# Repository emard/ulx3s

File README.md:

# ULX3S PCB

[ULX3S](http://radiona.org/ulx3s) = [University digital Logic](https://www.fer.unizg.hr/en/course/diglog) Learning
Xtensible board release 3 with SDRAM,
Successor of [ULX2S](http://github.com/emard/ulx2s).

[Manual](/doc/MANUAL.md) *
[Quickstart Binaries](http://github.com/emard/ulx3s-bin) *
[ULX3S at Kitspace](https://kitspace.org/boards/github.com/emard/ulx3s)

3D preview

Prototypes available
at [SKRIPTARNICA](http://skriptarnica.hr/vijest.aspx?newsID=1466),
local shop inside of [FER](https://www.fer.unizg.hr/) university.

This is a small (94x51 mm) standalone FPGA board 
for education, research and general purpose, with a full 
featured selection of chips which I all wanted on
a low-cost PCB, but haven't found on the market.
It's open source and open hardware because if it is
good for our development of [f32c](http://github.com/f32c/f32c) SOC,
it should be also good to other projects.

ULX3S will carry all digital logic on our
research, [education](https://www.fer.unizg.hr/en/course/diglog) and
[makerspace](https://radiona.org) projects in next 5 years.

ULX3S is standalone embeddable gadget with onboard display, buttons,
storage, WiFi and compatible connectors.

ULX3S can do things no other board can.

ULX3S can self-reflash with a bitstream sent
remotely from web interface over WiFi or from SD
card browsed by onboard OLED display and buttons.

ULX3S can completely power down and wakeup from
battery backed RTC.

ULX3S has rich range of chips and connectivity
required for many other open source projects:
SDRAM, USB, PS/2, SDCARD, Digital Video, FLASH, RTC, I2C, OLED, AUDIO, ADC,
onboard FM/ASK antenna 88-433.92 MHz and 56 GPIO pins routed as differential
pairs and have pinout that is PMOD compatible. There are 12 true
differential bidirectional pairs and 16 single-ended pairs.

ULX3S is sufficiently equipped to
emulate [Amiga](https://github.com/emard/Minimig_ECS) retro
computer and run its games, but can do much more like
running [Linux](https://twitter.com/fpga_dave/status/1053290842809683968).

[Schematics](/doc/schematics.pdf) and PCB started with KiCAD 4.
After version v1.8 project switched to KiCAD 5 PCB editor:

    kicad ulx3s.pro

View generated gerbers

    gerbv -p plot/ulx3s.gvp

# Features

FPGA: Lattice ECP5 [LFE5U-85F-6BG381C](http://www.latticesemi.com/view_document?document_id=50461) (12/25/45/85K LUT)

USB: FTDI [FT231XS](https://www.ftdichip.com/Support/Documents/DataSheets/ICs/DS_FT231X.pdf) (500kbit JTAG and 3Mbit USB-serial)

GPIO: 56 pins (12 true differential pairs, 16 single-ended pairs),
[PMOD](https://reference.digilentinc.com/_media/pmod:pmod:originalPmodInterfaceSpecification.pdf) compatible
with power out 3.3V/1A 2.5V/1.5A

RAM: 16-bit SDRAM [MT48LC32M16](https://www.micron.com/-/media/client/global/Documents/Products/Data%20Sheet/DRAM/256Mb_sdr.pdf) (8/16/32/64 MB)

Flash: Quad-SPI Flash [IS25LP128F](http://www.issi.com/WW/pdf/25LP-WP128F.pdf) (4/8/16 MB for FPGA config and user data)

Storage: Micro-SD slot

LEDs: 11 (8 blink-LEDs, 2 USB LEDs, 1 WiFi LED)

Buttons: 7 (4 direction, 2 fire, 1 power button)

Audio: 3.5 mm jack with 4 contacts (analog stereo + digital audio or composite video)

Video: GPDI connector with 3.3V-5V I2C bidirectional level shifter

Display: placeholder for 0.96" SPI COLOR OLED [SSD1331](https://drive.google.com/file/d/0B5lkVYnewKTGRlpxcEdWaXNvWnM/view)

WiFi+bluetooth: placeholder for [ESP-32](https://www.espressif.com/sites/default/files/documentation/esp32_datasheet_en.pdf) (Standalone JTAG web interface over WiFi)

Antenna: 88-108/433 MHz FM/ASK onboard

ADC: 8 channels, 12 bit, 1 MSa/s [MAX11125](https://datasheets.maximintegrated.com/en/ds/MAX11120-MAX11128.pdf) (4/8-ch, 8/10/12-bit, 0.5/1 MSa/s)

Power: 3 Switching voltage regulators: 1.1V, 2.5V, 3.3V (1.5/2A)

Clock: 25 MHz onboard, external differential clock input

Low power sleep: 5uA/5V standby, RTC [MCP7940N](http://ww1.microchip.com/downloads/en/DeviceDoc/20005010F.pdf) clock wakeup, power button, 32768 Hz quartz and battery

GPDI is General Purpose Differential Interface,
Electrically LVDS, mostly TMDS tolerant
female receptacle more-or-less compatible
with digital monitors/TVs

# Production

Independent production
like [q3k](https://twitter.com/q3k/status/1029010026269167618) or
[samlittlewood](https://twitter.com/samlittlewood/status/1108531208001077250) is
welcome and desirable under conditions of [modified MIT LICENSE](/LICENSE.md).
If you do manual assembly here is [minimal parts list](/doc/MINIMAL.md).

ZIP the gerbers and send them to manufacturer:

    zip -r /tmp/ulx3s.zip plot/ulx3s

If you are going to order this project by yourself, it is important
what manufacturer to choose for PCBA (PCB and Assembly) service.

Parts can be ordered from [Detailed BOM](/doc/ulx3s_bom.csv)
or from [ULX3S at Kitspace](https://kitspace.org/boards/github.com/emard/ulx3s),
which automatically submits [Simplified 1-click BOM](/1-click-bom.tsv) by
clicking on "Digikey" or "Mouser" button. On each click, Digikey and Mouser will keep
accumulating the BOM in the shopping cart. Number of unique parts on Digikey and Mouser
should be equal but DigiKey may split some parts (LEDs) in multiple rows.
To reset shopping cart, click "New Cart" or "New Basket".
Kitspace may be updated with about 1 day delay after this project update.

Choose PCBA manufacturer which can produce PCB of IPC CLASS 3 quality,
5/5 mil trace resolution and 0.2 mm holes.
Avoid manufacturer who claims "quality" and "satisfaction" but doesn't
really know what will be IPC CLASS rating for this project.

PCBA manufacturer prices for the parts should be approximately equal as those
from distributors like [Mouser](http://www.mouser.com) or [DigiKey](http://www.digikey.com).
Avoid any PCBA manufacturer who asks 3$ for the 1$ part or 40$ for the 30$ part.
Select [Mouser](http://www.mouser.com) language/location icon to PCBA manufacturer
country of origin and $-currency to check is PCBA manufacturer telling the truth
about prices.

Before soldering the parts, ask manufacturer for [pictures](/pic/ulx3sb-v18.jpg) of PCB.
CLASS 3 demands, among other things, that all drill holes stay inside of VIA pads.
If some holes [break-out](/pic/ulx3sb-v18-breakout-c19.png) from pads,
ask manufacturer to make new PCBs with better drill and copper layer alignment.

[PCBCART](http://www.pcbcart.com) offers CLASS 3 quality and assembly at reasonable cost.
Prices for the parts are equal to [Mouser](http://www.mouser.com).

Don't pay everything at once. Following payment phases during the
PCBA production are recommended:

    1. Pay for the parts
    2. Manufacturer orders the parts and optionally negotiates with you about part numbers.
       Depending on market availability, some parts may come in different physical package.
    3. Send updated gerbers which fit to ordered parts.
    4. Pay for PCB
    5. Manufacturer sends pictures of produced PCB for your inspection.
       If anything looks suspicious, ask also for X-ray imaging.
    6. Pay for the assembly and shipping.

Nobody wants quality issues, so it is good to ask if manufacturer has qualified personnel
able to follow instructions 
for [ULX3S self-test](https://github.com/emard/ulx3s-bin) before shipping.
## This readme clearly shows how to use make the project step by step in simple ways happy making :)

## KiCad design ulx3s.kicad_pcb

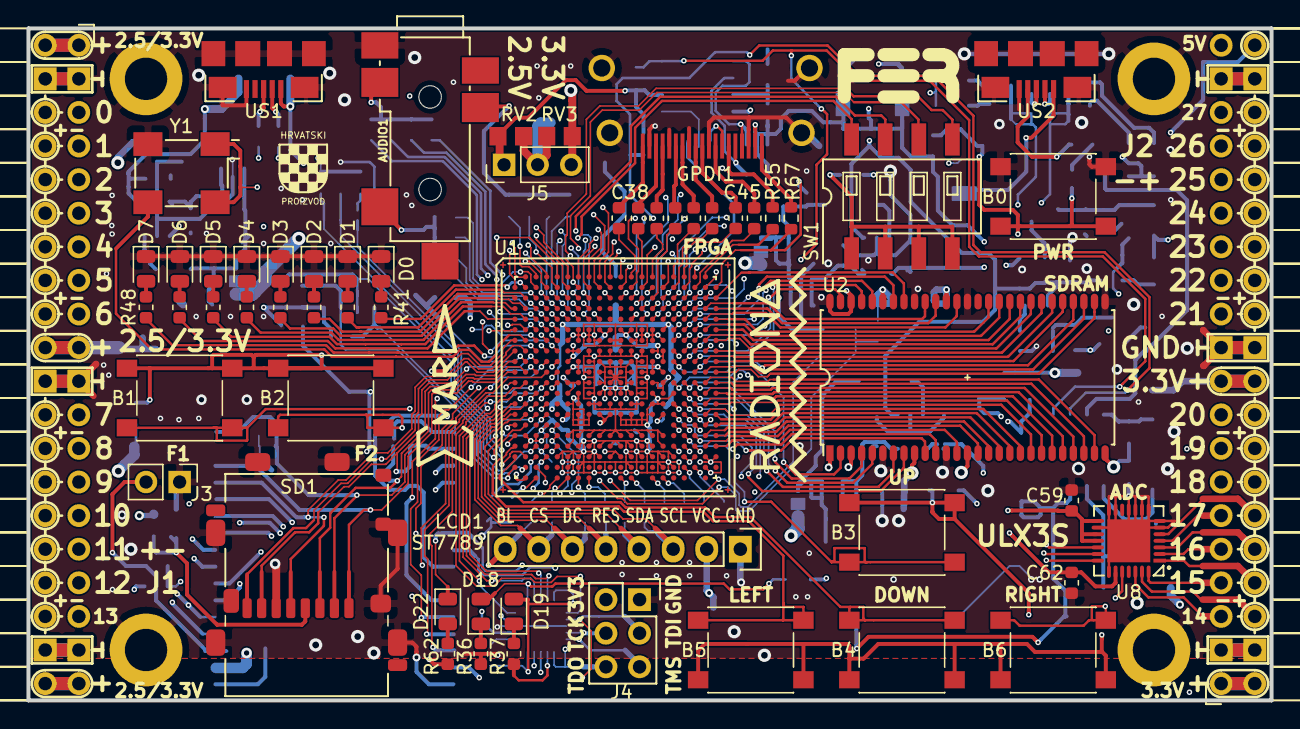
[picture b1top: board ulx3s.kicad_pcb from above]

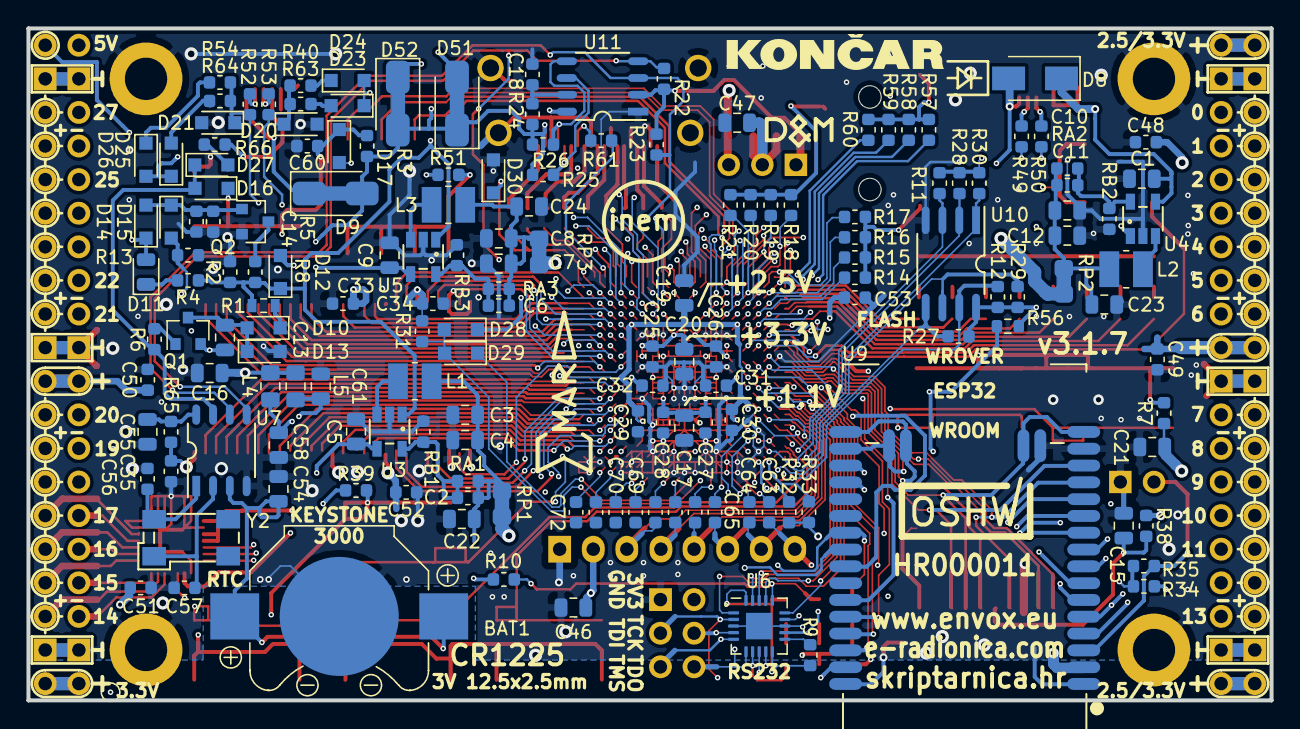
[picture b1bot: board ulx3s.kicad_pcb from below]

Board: 4 copper layers, 94.0 x 50.8 mm, 234 parts (167 on the bottom side), 287 nets.

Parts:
AE1: 433MHz; TestPoint_Pad_D1.0mm
AUDIO1: JACK_TRS_6PINS; CUI_SJ-43516-SMT
B0, B1, B2, B3, B4, B5, B6: PTS645; SW_SPST_PTS645
BAT1: CR1225; Keystone_3000_1x12mm-CoinCell
C1, C3, C4, C5, C7, C8, C9, C11, C12, C15, C21, C54, C55, C58, C61: 22uF; C_0805_2012Metric
C2, C6, C10, C18: 100pF; C_0603_1608Metric
C13, C16, C17, C19, C20, C22, C23, C24, C46, C47: 2.2uF; C_0805_2012Metric
C14, C59, C60, C62: 220nF; C_0603_1608Metric
C25, C26, C27, C28, C29, C30, C31, C32, C33, C34, C35, C38, C39, C40, C41, C42, C43, C44, C45, C48, C49, C50, C51, C52, C53, C63, C64, C65, C66, C67, C68, C69, C70, C71, C72: 22nF; C_0603_1608Metric
C56, C57: 4.7pF; C_0603_1608Metric
D0, D4, D11, D19: RED; LED_0805_2012Metric
D1, D5: ORANGE; LED_0805_2012Metric
D2, D6, D18: GREEN; LED_0805_2012Metric
D3, D7, D22: BLUE; LED_0805_2012Metric
D8: STPS2L40AF; D_SMA
D9, D51, D52: 0; D_SMA_Jumper_NC
D10, D13, D14, D16, D17, D23, D24, D25, D26, D27, D28, D29: 1N914; D_SOD-323_HandSoldering
D12, D15: BAT54W; D_SOD-323_HandSoldering
D20, D21, D30: 3.6V; D_SOD-323_HandSoldering
D&M: dm2mm
EMARD: emard12mm
EMARD#2: emard12mm
GPDI1: GPDI-D; CONN-10029449-111RLF
H1, H2, H3, H4: HOLE; MountingHole_3.2mm_M3_ISO14580_Pad
HR: HR; hrvatski
J1, J2: CONN_02X20; Socket_Strip_Angled_2x20
J3: WIFI_OFF; PinHeader_1x02_P2.54mm_Vertical
J4: CONN_02X03; Socket_Strip_Straight_2x03
J5: VJ1; PinHeader_1x03_P2.54mm_Vertical
L1, L2, L3: 2.2uH; L_1008_1210
L4, L5: 33uH; L_0805_2012Metric_Pad1.15x1.40mm_HandSolder
LCD1: ST7789; st7789
OSHW: OSHW2mm; oshw
Q1: BC857; SOT-23
Q2: 2N7002; SOT-23
R1, R3, R4, R25, R26, R30: 4.7k; R_0603_1608Metric
R2: 18k; R_0603_1608Metric
R5: 2.2M; R_0603_1608Metric
R6, R8, R14, R18, R29, R40, R54, R57, R66: 1.1k; R_0603_1608Metric
R7, R10, R17, R21, R39, R51, R60: 130; R_0603_1608Metric
R9, R13, R31, R32, R33, R34, R56, R63, R64: 15k; R_0603_1608Metric
R11, R12, R27, R28, R55: 10k; R_0603_1608Metric
R15, R19, R35, R36, R37, R41, R42, R43, R44, R45, R46, R47, R48, R58, R61, R62, R65, R67: 549; R_0603_1608Metric
R16, R20, R59: 270; R_0603_1608Metric
R22, R23: 3.3k; R_0603_1608Metric
R24: 100k; R_0603_1608Metric
R38: 0.47; R_0603_1608Metric
R49, R50, R52, R53: 27; R_0603_1608Metric
RA1, RA2, RA3: 15k; R_0603_1608Metric
RB1: 18k; R_0603_1608Metric
RB2: 4.7k; R_0603_1608Metric
RB3: 3.3k; R_0603_1608Metric
RP1, RP2, RP3: 0; R_0805_2012Metric_Pad1.29x1.40mm_HandSolder_Jumper_NC
RV2, RV3: 0; R_0805_2012Metric_Pad1.29x1.40mm_HandSolder
SD1: 104031-0811; SCHD3A100-104031-0811
SW1: SW_DIP_x04; SW_DIP_x4_W8.61mm_Slide_LowProfile
U1: LFE5U-85F-6BG381C; BGA-381_pitch0.8mm_dia0.4mm
U2: MT48LC16M16A2TG; TSOP54
U3, U4, U5: TLV62569DBV; TSOT-25
U6: FT231XQ; FT231X-QFN-20-1EP_4x4mm_P0.5mm_EP2x2mm
U7: MCP7940NT; SOT96-1
U8: MAX11125; MAX1112x-TQFN-28-1EP_5x5mm_Pitch0.5mm
U9: ESP32
U10: IS25LP128F-JBLE; SOA008-150-208mil
U11: PCA9306D; SM8
US1, US2: MICRO_USB; USB-MICRO-B-FCI-10118192-0001LF
Y1: FNETHE025; Crystal_SMD_7050_4Pads
Y2: 32768Hz; Crystal_SMD_ABS25
fer: fer; fer4mm6
koncar: koncar
radiona: radiona

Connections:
2V5_3V3: C26.1, C47.1, C48.1, C49.1, C53.1, J1.1, J1.2, J1.19, J1.20, J1.39, J1.40, J5.2, R51.1, RV2.2, RV3.1, U1.F9, U1.F10, U1.H6, U1.H7, U1.J6
+1V1: C17.1, C27.1, C28.1, RP1.2, U1.H8, U1.H9, U1.H10, U1.H11, U1.H12, U1.H13, U1.J8, U1.J13, U1.K8, U1.K13, U1.L8, U1.L13, U1.M8, U1.M13, U1.N8, U1.N9, U1.N10, U1.N11, U1.N12, U1.N13, U1.T6, U1.T7, U1.T8, U1.T9, U1.T10, U1.T11, U1.T12, U1.T13, U1.T14, U1.T15, U1.U6, U1.U15
+2V5: C19.1, C29.1, C30.1, J5.1, R22.1, R23.1, RP2.2, RV2.1, U1.F6, U1.F15, U1.P6, U1.P15, U1.V10, U1.V11, U1.V17, U1.V18, U11.2
+3V3: C16.1, C20.1, C21.1, C25.1, C31.1, C32.1, C33.1, C34.1, C35.1, C46.1, C50.1, C51.1, C52.1, D11.2, D14.1, J2.1, J2.2, J2.19, J2.20, J4.2, J5.3, L4.1, L5.1, LCD1.2, R7.1, R11.1, R12.1, R27.1, R28.1, R29.1, R30.1, R31.1, R32.1, R33.1, R34.1, R38.2, R39.1, R56.1, R62.2, R65.1, RP3.2, RV3.2, U1.F11, U1.F12, U1.H14, U1.H15, U1.J15, U1.L6, U1.L7, U1.L14, U1.L15, U1.M6, U1.M15, U1.P9, U1.P10, U1.T2, U1.T3, U1.T4, U1.U2, U2.1, U2.3, U2.9, U2.14, U2.27, U2.43, U2.49, U9.2, U10.8, U11.8, Y1.1, Y1.4
+5V: C1.1, C5.1, C9.1, C13.1, D8.1, D9.2, D51.1, D52.2, GPDI1.18, Q1.2, R3.1, R24.1, R25.1, R26.1, U3.4, U4.4, U5.4
/analog/ADC3V3: C58.1, C59.1, L4.2, U8.15, U8.17, U8.18
/analog/ADCD3V3: C61.1, C62.1, L5.2, U8.23
/analog/AUDIO_L: AUDIO1.2, R14.2, R15.2, R16.2, R17.2
/analog/AUDIO_R: AUDIO1.3, R18.2, R19.2, R20.2, R21.2
/analog/AUDIO_V: AUDIO1.4, R57.2, R58.2, R59.2, R60.2
/blinkey/ALED0: D0.2, R41.2
/blinkey/ALED1: D1.2, R42.2
/blinkey/ALED2: D2.2, R43.2
/blinkey/ALED3: D3.2, R44.2
/blinkey/ALED4: D4.2, R45.2
/blinkey/ALED5: D5.2, R46.2
/blinkey/ALED6: D6.2, R47.2
/blinkey/ALED7: D7.2, R48.2
/blinkey/BTNPUL: B1.1, B2.1, R7.2
/blinkey/BTNPUR: B3.1, B4.1, B5.1, B6.1, R39.2
/blinkey/LED_PWREN: D18.1, R36.1
/blinkey/LED_TXLED: D19.1, R37.2
/blinkey/LED_WIFI: D22.2, R62.1
/blinkey/SWPU: R51.2, SW1.1, SW1.2, SW1.3, SW1.4
/flash/FLASH_MISO: R28.2, U1.V2, U10.2
/flash/FLASH_MOSI: R27.2, U1.W2, U10.5
/flash/FLASH_SCK: R29.2, U1.U3, U10.6
/flash/FLASH_nCS: R30.2, U1.R2, U10.1
/flash/FLASH_nHOLD: R12.2, U1.W1, U10.7
/flash/FLASH_nWP: R11.2, U1.Y2, U10.3
/flash/FPGA_DONE: R32.2, U1.Y3
/flash/FPGA_INITN: R33.2, U1.V3
/flash/FPGA_PROGRAMN: D28.2, D29.2, R31.2, U1.W3
/gpdi/GPDI_CEC: GPDI1.13, R61.1
/gpdi/GPDI_CLK+: C44.2, GPDI1.10
/gpdi/GPDI_CLK-: C45.2, GPDI1.12
/gpdi/GPDI_D0+: C42.2, GPDI1.7
/gpdi/GPDI_D0-: C43.2, GPDI1.9
/gpdi/GPDI_D1+: C40.2, GPDI1.4
/gpdi/GPDI_D1-: C41.2, GPDI1.6
/gpdi/GPDI_D2+: C38.2, GPDI1.1
/gpdi/GPDI_D2-: C39.2, GPDI1.3
/gpdi/GPDI_HPD: GPDI1.19, R67.2
/gpdi/GPDI_UTIL: GPDI1.14, R55.2
/gpdi/VREF2: C18.1, R24.2, U11.7
/gpio/IN5V: D51.2, J2.39
/gpio/OUT5V: D52.1, J2.40
/power/FB1: C2.2, RA1.2, RB1.2, U3.5
/power/FB2: C10.2, RA2.2, RB2.2, U4.5
/power/FB3: C6.2, RA3.2, RB3.2, U5.5
/power/FTDI_nSUSPEND: D12.2, R10.1
/power/HOLD: D11.1, R4.1
/power/L1: L1.1, U3.3
/power/L2: L2.1, U4.3
/power/L3: L3.1, U5.3
/power/OSCI_32k: C56.2, U7.1, Y2.4
/power/OSCO_32k: C57.2, U7.2, Y2.1
/power/P1V1: C2.1, C3.1, C4.1, C22.1, L1.2, RA1.1, RP1.1
/power/P2V5: C10.1, C11.1, C12.1, C23.1, L2.2, RA2.1, RP2.1
/power/P3V3: C6.1, C7.1, C8.1, C24.1, L3.2, RA3.1, RP3.1
/power/PWREN: D12.1, R1.2, R2.1, R4.2, R8.1, U3.1, U4.1, U5.1
/power/RTCVDD: C55.1, R65.2, U7.8
/power/SHD: Q2.3, R8.2
/power/SHUT: C14.1, D14.2, D15.1, Q2.1, R5.1
/power/VBAT: BAT1.1, C54.1, U7.3
/power/WAKE: D10.1, R1.1
/power/WAKEUPn: D16.2, D27.1, R6.2, U7.7
/power/WKUP: C13.2, D10.2, D13.1, Q1.3
/power/WKn: Q1.1, R6.1
/serdes/SRCLKN: C68.1, U1.Y12
/serdes/SRCLKP: C67.2, U1.Y11
/serdes/SRXN00: C64.1, U1.Y6
/serdes/SRXN01: C66.1, U1.Y8
/serdes/SRXN10: C70.1, U1.Y15
/serdes/SRXP00: C63.2, U1.Y5
/serdes/SRXP01: C65.2, U1.Y7
/serdes/SRXP10: C69.2, U1.Y14
/serdes/STXN11: C72.1, U1.W18
/serdes/STXP11: C71.2, U1.W17
/usb/ANT_433MHz: AE1.1, U1.G1
/usb/FPD+: R53.2, US2.3
/usb/FPD-: R52.2, US2.2
/usb/FTD+: R50.2, US1.3
/usb/FTD-: R49.2, US1.2
/usb/US2VBUS: D9.1, US2.1
/wifi/SD3V3: C15.1, R38.1, SD1.4
/wifi/WIFIEN: J3.2, R35.2, U9.3
ADC_CSn: U1.R17, U8.20
ADC_MISO: U1.U16, U8.24
ADC_MOSI: U1.R16, U8.21
ADC_SCLK: U1.P17, U8.19
AUDIO_L0: R14.1, U1.E4
AUDIO_L1: R15.1, U1.D3
AUDIO_L2: R16.1, U1.C3
AUDIO_L3: R17.1, U1.B3
AUDIO_R0: R18.1, U1.A3
AUDIO_R1: R19.1, U1.B5
AUDIO_R2: R20.1, U1.D5
AUDIO_R3: R21.1, U1.C5
AUDIO_V0: R57.1, U1.H5
AUDIO_V1: R58.1, U1.F2
AUDIO_V2: R59.1, U1.F5
AUDIO_V3: R60.1, U1.E5
BTN_D: B4.2, U1.V1
BTN_F1: B1.2, U1.R1
BTN_F2: B2.2, U1.T1
BTN_L: B5.2, U1.U1
BTN_PWRn: D17.2, U1.D6
BTN_R: B6.2, U1.H16
BTN_U: B3.2, U1.R18
CLK_25MHz: U1.G2, Y1.3
FPDI_CEC: R61.2, U1.A18
FPDI_CLK+: C44.1, U1.A17
FPDI_CLK-: C45.1, U1.B18
FPDI_D0+: C42.1, U1.A16
FPDI_D0-: C43.1, U1.B16
FPDI_D1+: C40.1, U1.A14
FPDI_D1-: C41.1, U1.C14
FPDI_D2+: C38.1, U1.A12
FPDI_D2-: C39.1, U1.A13
FPDI_HPD: D30.1, R67.1, U1.B20
FPDI_SCL: R23.2, U1.E12, U7.6, U11.3
FPDI_SDA: R22.2, U1.B19, U7.5, U11.4
FPDI_UTIL: R55.1, U1.A19
FT2V5: D19.2, R9.2, U6.10, U6.20
FTDI_RXD: U1.L4, U6.1
FTDI_TXD: U1.M1, U6.17
FTDI_TXDEN: U1.L3, U6.15
FTDI_nDTR: U1.N1, U6.18
FTDI_nRTS: U1.M3, U6.19
FTDI_nRXLED: U1.L5, U6.14
FTDI_nSLEEP: D18.2, R10.2, U6.16
FTDI_nTXLED: R37.1, U6.7
GN0: J1.5, U1.C11
GN1: J1.7, U1.A11
GN2: J1.9, U1.B10
GN3: J1.11, U1.C10
GN4: J1.13, U1.A8
GN5: J1.15, U1.B8
GN6: J1.17, U1.C7
GN7: J1.23, U1.B6
GN8: J1.25, U1.A5
GN9: J1.27, U1.B1
GN10: J1.29, U1.B4
GN11: J1.31, U1.E3
GN12: J1.33, U1.F3, U9.8
GN13: J1.35, U1.G5, U9.5
GN14: J2.5, U1.U17, U8.26
GN15: J2.7, U1.P16, U8.28
GN16: J2.9, U1.M17, U8.2
GN17: J2.11, U1.L17, U8.4
GN18: J2.13, U1.H17
GN19: J2.15, U1.G18
GN20: J2.17, U1.E17
GN21: J2.23, U1.D17
GN22: J2.25, U1.C15
GN23: J2.27, U1.C17
GN24: J2.29, U1.D16
GN25: J2.31, U1.E14
GN26: J2.33, U1.C13
GN27: J2.35, U1.E13
GND: AUDIO1.1, B0.2, BAT1.2, C1.2, C3.2, C4.2, C5.2, C7.2, C8.2, C9.2, C11.2, C12.2, C14.2, C15.2, C16.2, C17.2, C18.2, C19.2, C20.2, C21.2, C22.2, C23.2, C24.2, C25.2, C26.2, C27.2, C28.2, C29.2, C30.2, C31.2, C32.2, C33.2, C34.2, C35.2, C46.2, C47.2, C48.2, C49.2, C50.2, C51.2, C52.2, C53.2, C54.2, C55.2, C56.1, C57.1, C58.2, C59.2, C60.2, C61.2, C62.2, D0.1, D1.1, D2.1, D3.1, D4.1, D5.1, D6.1, D7.1, D13.2, D20.2, D21.2, D30.2, GPDI1.0, GPDI1.2, GPDI1.5, GPDI1.8, GPDI1.11, GPDI1.17, H1.1, H2.1, H3.1, H4.1, J1.3, J1.4, J1.21, J1.22, J1.37, J1.38, J2.3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
GP0: J1.6, U1.B11
GP1: J1.8, U1.A10
GP2: J1.10, U1.A9
GP3: J1.12, U1.B9
GP4: J1.14, U1.A7
GP5: J1.16, U1.C8
GP6: J1.18, U1.C6
GP7: J1.24, U1.A6
GP8: J1.26, U1.A4
GP9: J1.28, U1.A2
GP10: J1.30, U1.C4
GP11: J1.32, U1.F4
GP12: J1.34, U1.G3, U9.9
GP13: J1.36, U1.H4, U9.4
GP14: J2.6, U1.U18, U8.27
GP15: J2.8, U1.N17, U8.1
GP16: J2.10, U1.N16, U8.3
GP17: J2.12, U1.L16, U8.5
GP18: J2.14, U1.H18
GP19: J2.16, U1.F17
GP20: J2.18, U1.D18
GP21: J2.24, U1.C18
GP22: J2.26, U1.B15
GP23: J2.28, U1.B17
GP24: J2.30, U1.C16
GP25: J2.32, U1.D14
GP26: J2.34, U1.B13
GP27: J2.36, U1.D13
GPDI_SCL: GPDI1.15, R25.2, U11.6
GPDI_SDA: GPDI1.16, R26.2, U11.5
JTAG_TCK: J4.4, U1.T5, U6.4, U9.30
JTAG_TDI: J4.3, U1.R5, U6.2, U9.37
JTAG_TDO: J4.6, U1.V4, U6.6, U9.6
JTAG_TMS: D22.1, J4.5, U1.U5, U6.5, U9.29
LED0: R41.1, U1.B2
LED1: R42.1, U1.C2
LED2: R43.1, U1.C1
LED3: R44.1, U1.D2
LED4: R45.1, U1.D1
LED5: R46.1, U1.E2
LED6: R47.1, U1.E1
LED7: R48.1, U1.H3
unnamed: D23.2, R63.1
unnamed: D24.1, R40.1
unnamed: D25.2, R64.1
unnamed: D26.1, R54.2
unnamed: D27.2, R66.2
OLED_BL: C63.1, LCD1.8, U1.J4
OLED_CLK: C68.2, LCD1.3, U1.P4
OLED_CS: C64.2, LCD1.7, U1.N2
OLED_DC: C65.1, LCD1.6, U1.P1
OLED_MOSI: C67.1, LCD1.4, U1.P3
OLED_RES: C66.2, LCD1.5, U1.P2
PWRBTn: B0.1, C60.1, D16.1, D17.1, D28.1, R3.2
SDRAM_A0: U1.M20, U2.23
SDRAM_A1: U1.M19, U2.24
SDRAM_A2: U1.L20, U2.25
SDRAM_A3: U1.L19, U2.26
SDRAM_A4: U1.K20, U2.29
SDRAM_A5: U1.K19, U2.30
SDRAM_A6: U1.K18, U2.31
SDRAM_A7: U1.J20, U2.32
SDRAM_A8: U1.J19, U2.33
SDRAM_A9: U1.H20, U2.34
SDRAM_A10: U1.N19, U2.22
SDRAM_A11: U1.G20, U2.35
SDRAM_A12: U1.G19, U2.36
SDRAM_BA0: U1.P19, U2.20
SDRAM_BA1: U1.N20, U2.21
SDRAM_CKE: U1.F20, U2.37
SDRAM_CLK: U1.F19, U2.38
SDRAM_D0: U1.J16, U2.2
SDRAM_D1: U1.L18, U2.4
SDRAM_D2: U1.M18, U2.5
SDRAM_D3: U1.N18, U2.7
SDRAM_D4: U1.P18, U2.8
SDRAM_D5: U1.T18, U2.10
SDRAM_D6: U1.T17, U2.11
SDRAM_D7: U1.U20, U2.13
SDRAM_D8: U1.E19, U2.42
SDRAM_D9: U1.D20, U2.44
SDRAM_D10: U1.D19, U2.45
SDRAM_D11: U1.C20, U2.47
SDRAM_D12: U1.E18, U2.48
SDRAM_D13: U1.F18, U2.50
SDRAM_D14: U1.J18, U2.51
SDRAM_D15: U1.J17, U2.53
SDRAM_DQM0: U1.U19, U2.15
SDRAM_DQM1: U1.E20, U2.39
SDRAM_nCAS: U1.T19, U2.17
SDRAM_nCS: U1.P20, U2.19
SDRAM_nRAS: U1.R20, U2.18
SDRAM_nWE: U1.T20, U2.16
SD_CLK: SD1.5, U1.H2, U9.13
SD_CMD: SD1.3, U1.J1, U9.23
SD_D0: SD1.7, U1.J3, U9.24
SD_D1: SD1.8, U1.H1, U9.26
SD_D2: SD1.1, U1.K1, U9.14
SD_D3: SD1.2, U1.K2, U9.16
SHUTDOWN: D15.2, R13.1, U1.G16
SW1: SW1.8, U1.E8
SW2: SW1.7, U1.D8
SW3: SW1.6, U1.D7
SW4: SW1.5, U1.E7
US2_ID: R66.1, US2.4
USB5V: D8.2, U6.12, US1.1
USB_FPGA_D+: D20.1, R40.2, R53.1, R63.2, U1.D15, U1.E16
USB_FPGA_D-: D21.1, R52.1, R54.1, R64.2, U1.E15, U1.F16
USB_FPGA_PULL_D+: D23.1, D24.2, U1.B12
USB_FPGA_PULL_D-: D25.1, D26.2, U1.C12
USB_FTDI_D+: R50.1, U6.8
USB_FTDI_D-: R49.1, U6.9
USER_PROGRAMN: D29.1, U1.M4
WIFI_EN: R34.2, R35.1, U1.J5
WIFI_GPIO0: R56.2, U1.F1, U9.25
WIFI_GPIO19: U1.N4, U9.31
WIFI_GPIO21: U1.K5, U9.33
WIFI_GPIO22: U1.L2, U9.36
WIFI_GPIO25: U1.E9, U9.10
WIFI_GPIO26: U1.L1, U9.11
WIFI_GPIO27: U1.N3, U9.12
WIFI_GPIO35: U1.E6, U9.7
WIFI_RXD: U1.K3, U9.34
WIFI_TXD: U1.K4, U9.35
nRESET: R9.1, U6.11

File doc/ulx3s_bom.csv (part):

Component,Description,Part,References,Value,Footprint,Quantity Per PCB,Datasheet,Koncar,Vertical,MNF1_URL,MPN,MFG1,Digikey,price100_Vertical,Side,Mouser,price700_LCSC,LCSC,price100_RS,RS,MPN3,Digike_y3,MNF3_URL,Digike_y2,MPN2,MFG2,MFG3,Datasheet3,MNF2_URL,Mouse_r2,price1500_Mouser,Mouse_r3,Mouse_r4,Mouse_r5,price1200_Chip1stop,Chip1stop,price200_Mouser,MP_N3,MP_N2,Datasheet2,LowCost,price300_LCSC,TME,price300_TME,price200_LCSC,price400_LCSC,Mouser_URL,price100_AvnetEU,AvnetEU,price100_Mouser,price100_Onlinecomponents,Onlinecomponents,price300_Vertical,DatasheetLC,MP_N4,MFG4,MP_N5,price_Arrow,Arrow,price100_LCSC,Aliexpress,Dtasheet4,MPN4,MNF4_URL,price100_Mouse,Footprint_URL,price100_Digikey,Datasheet_errata,MFG2_TR_DS,price100_Arrow,Datasheet4,price100_Mouse_r2,price100_Newark,Newark,FreelanceElec,Digikey2,price200_FreelanceElec,price100_TME
1,audio jack TRS 6 pins apple/nokia,JACK_TRS_6PINS_APPLE,AUDIO1,JACK_TRS_6PINS,CUI_SJ-43516-SMT,1,http://www.cui.com/product/resource/sj-4351x-smt-series.pdf,FAU001,SJ-43516-SMT-TR,www.cui.com,SJ-43516-SMT-TR,CUI,CP-43516SJCT-ND,0.8015$,T,490-SJ-43516-SMT-TR,,,,,,,,,,,,,,,,,,,,,,,,,,,,,,,,,,,,,,,,,,,,,,,,,,,,,,,,,,,,,,
2,"Push button switch, generic, two pins",SW_Push,B0 B1 B2 B3 B4 B5 B6,PTS645,SW_SPST_PTS645,7,http://www.ckswitches.com/media/1471/pts645.pdf,FSW001,,www.ckswitches.com,PTS645SL50SMTR92 LFS,,CKN9088CT-ND,,T,611-PTS645SL50SMTR92,0.09966$,C221877,,,,,,,,,,,,,,,,,,,,,,,,,,,,,,,,,,,,,,,,,,,,,,,,,,,,,,,,,,,,
3,Single-cell battery,Battery_Cell,BAT1,CR1225,Keystone_3000_1x12mm-CoinCell,1,http://www.keyelco.com/product-pdf.cfm?p=777,FBAT001,,www.keyelco.com,3000TR,Keystone,BK-885-ND,,,855-S8201-46R,,,0.33296$,1613707,S8201-46R,952-1662-1-ND,www.harwin.com,36-3000CT-ND,BK-885,MPD,Harwin,https://cdn.harwin.com/pdfs/S8201R.pdf,www.memoryprotectiondevices.com,,,,,,,,,,,,,,,,,,,,,,,,,,,,,,,,,,,,,,,,,,,,,,,,,
4,Unpolarized capacitor,C,C13 C16 C17 C19 C20 C22 C23 C24 C46 C47,2.2uF,C_0805_2012Metric,10,,FC001,,www.yageo.com,CC0805MRX5R6BB225,,587-5918-1-ND,,,80-C0805C225K4R3123,,,,,,,,1276-2903-1-ND,,,,,,603-CC805MRX5R6BB225,,,,,,,,,,,,,,,,,,,,,,,,,,,,,,,,,,,,,,,,,,,,,,,,
5,Unpolarized capacitor,C,C14 C36 C37 C38 C39 C40 C41 C42 C43 C44 C45 C59 C60 C62,220nF,C_0603_1608Metric,14,,FC002,,www.yageo.com,CC0603KRX7R8BB224,,1276-1112-1-ND,,TB,81-GCM188R71E224K55D,,,,,,,,,,,,,,603-CC603KRX7R6BB224,,,,,,,,,,,,,,,,,,,,,,,,,,,,,,,,,,,,,,,,,,,,,,,,
6,Unpolarized capacitor,C,C25 C26 C27 C28 C29 C30 C31 C32 C33 C34 C35 C48 C49 C50 C51 C52 C53,22nF,C_0603_1608Metric,17,,FC003,,www.yageo.com,CC0603JRX7R8BB223 CX0603MRX7R8BB223,,587-1238-1-ND,,,603-CC603JRX7R8BB223,,,,,,,,1276-2000-1-ND,,,,,,603-AC603KRX7R7BB223,35.7$,,,,,,,,,,,,,,,,,,,,,,,,,,,,,,,,,,,,,,,,,,,,,,,
7,Unpolarized capacitor,C,C1 C3 C4 C5 C7 C8 C9 C11 C12 C15 C21 C54 C55 C58 C61,22uF,C_0805_2012Metric,15,,FC004,,www.yageo.com,CC0805ZKY5V5BB226,,1276-2413-1-ND,,,81-GRM21BR61A226ME1L,,,,,,,,1276-2412-1-ND,,,,,,81-GRM21BR61A226ME1K,,81-GRM219R61C226ME5L,81-GRM188C60J226ME0J,963-LMK212BBJ226MG-T,,,,,,,,,,,,,,,,,,,,,,,,,,,,,,,,,,,,,,,,,,,,
8,Unpolarized capacitor,C,C56 C57,3.3pF,C_0603_1608Metric,2,,FC005,,www.yageo.com,CC0603CRNPO9BN3R3,,311-3848-1-ND,,,710-885012006048,,,,,,,,311-3855-1-ND,,,,,,,,,,,,,,,,,,,,,,,,,,,,,,,,,,,,,,,,,,,,,,,,,,,,,,
9,Unpolarized capacitor,C,C2 C6 C10 C18,470pF,C_0603_1608Metric,4,,FC006,,www.yageo.com,CS0603KRX7R9BB471,,399-9086-1-ND,,,603-CC603KRX7R9BB471,,,,,,,,,,,,,,603-CS0603KRX79BB471,,,,,,,,,,,,,,,,,,,,,,,,,,,,,,,,,,,,,,,,,,,,,,,,
10,Diode,D,D10 D13 D14 D16 D17 D23 D24 D25 D26 D27 D29,1N914,D_SOD-323_HandSoldering,11,,FV001,,www.fairchildsemi.com,1N4148WS,,1N914BWSCT-ND,,,863-MMDL914T1G,,,,,,1N4148WXTPMSCT-ND,,1N4148WSFSCT-ND,,,,,,,,,,,0.01209$,C1S541901230010,,,,,,,,,,,,,,,,,,,,,,,,,,,,,,,,,,,,,,,,,,
11,"Zener diode, small symbol, filled shape",D_Zener_Small_ALT,D20 D21,3.6V,D_SOD-323_HandSoldering,2,http://www.taiwansemi.com/products/datasheet/BZT52C2V4S%20SE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,FV002,,www.taiwansemi.com,BZT52C3V6S,,BZT52C3V6S-TPMSCT-ND,,,833-BZT52C3V6S-TP,,,,,,,,,,,,,,,,,,,,,0.096$,,,,,,,,,,,,,,,,,,,,,,,,,,,,,,,,,,,,,,,,,
12,Schottky diode,D_Schottky,D12 D15,BAT54W,D_SOD-323_HandSoldering,2,,FV003,,www.onsemi.com,NSR0530HT1G,ON semiconductor,NSR0530HT1GOSCT-ND,,,755-RSX051VYM30FHTR,,,,,,,,,BAT54WSQ-7-F,Diodes inc.,,,www.diodes.com,,,,,,,,0.093$,,,,,,,,,,,,,,,,,,,,,,,,,,,,,,,,,,,,,,,,,
13,Light emitting diode,LED,D22,BLUE,LED_0805_2012Metric,1,http://optoelectronics.liteon.com/upload/download/DS-22-99-0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,FV004,,www.liteon.com,LTST-C170TBKT,,160-1579-1-ND,,T,859-LTST-C170TBKT,,,,,,,,,,,,https://www.rohm.com/datasheet/SML-M13UT,,755-SMLMN2BCTT86C,,859-LTST-C171TBKT,,,,,,SMLMN2BCTT86C,LTST-C171TBKT,http://optoelectronics.liteon.com/upload/download/ds22-2000-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,,,,,,,,,,,,,,,,,,,,,,,,,,,,,,,,,,,,,,
14,"Light emitting diode, filled shape",LED_ALT,D3 D7,BLUE,LED_0805_2012Metric,2,http://optoelectronics.liteon.com/upload/download/DS-22-99-0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,FV004,,www.liteon.com,LTST-C170TBKT,,160-1579-1-ND,,T,859-LTST-C170TBKT,,C98222,,,,,,,,,,https://www.rohm.com/datasheet/SML-M13UT,,755-SMLMN2BCTT86C,,859-LTST-C171TBKT,,,,,,SMLMN2BCTT86C,LTST-C171TBKT,http://optoelectronics.liteon.com/upload/download/ds22-2000-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,LTST-C170KRKT,0.02930$,,,,,,,,,,,,,,,,,,,,,,,,,,,,,,,,,,,,
15,Light emitting diode,LED,D18,GREEN,LED_0805_2012Metric,1,http://optoelectronics.liteon.com/upload/download/DS22-2000-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,FV005,,www.liteon.com,LTST-C170TGKT,,160-1887-1-ND,,T,859-LTST-C170TGKT,,,,,,,,,,,,,,,,,,,,,,,,,,,,,,,,,,,,,,,,,,,,,,,,,,,,,,,,,,,,,,
16,"Light emitting diode, filled shape",LED_ALT,D2 D6,GREEN,LED_0805_2012Metric,2,http://optoelectronics.liteon.com/upload/download/DS22-2000-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,FV005,,www.liteon.com,LTST-C170TGKT,,160-1887-1-ND,,T,859-LTST-C170TGKT,,,,,,,,,,,,,,,,,,,,,,,,,LTST-C170KRKT,,LTST-C170TGKT,0.0789$,,,,,,,,,,,,,,,,,,,,,,,,,,,,,,,,,,
17,"Light emitting diode, filled shape",LED_ALT,D1 D5,ORANGE,LED_0805_2012Metric,2,https://optoelectronics.liteon.com/upload/download/DS-22-99-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,FV006,,www.liteon.com,LTST-C170KFKT,,160-1413-1-ND,,T,859-LTST-C170KFKT,,C284931,,,,,,,,,,,,,,,,,,,,,,,LTST-C170KRKT,,,,0.02075$,,,,,,,,,,,,,,,,,,,,,,,,,,,,,,,,,
18,"Light emitting diode, filled shape",LED_ALT,D0 D4 D11 D19,RED,LED_0805_2012Metric,4,https://optoelectronics.liteon.com/upload/download/DS-22-99-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,FV007,,www.liteon.com,LTST-C170KRKT,,160-1415-1-ND,,TB,859-LTST-C170KRKT,,C94868,,,,,,,,,,,,,,,,,,,,,,,,,,,,0.0195$,www.mouser.com,,,,,,,,,,,,,,,,,,,,,,,,,,,,,,,
19,"Schottky diode, small symbol",D_Schottky_Small,D8,STPS2L30AF,D_SMA,1,,FV008,,www.st.com,STPS2L30AF,,497-12310-1-ND,,,511-STPS2L30AF,,,,,,,,,,,,,,,,,,,,,,,,,,,,,,,,0.22121$,STPS2L30AF,,,,,,,,,,,,,,,,,,,,,,,,,,,,,
20,HDMI-D,HDMI-D,GPDI1,GPDI-D,CONN-10029449-111RLF,1,http://portal.fciconnect.com/Comergent/fci/drawing/10029449.pdf,FX001,,www.amphenol-icc.com,10029449-111RLF,,609-4614-1-ND,,T,649-10029449-111RLF,,,,,,,,A136174CT-ND,5-1903015-5,,,,www.te.com,,,,,,,,,,,https://hr.mouser.com/datasheet/2/418/NG_CD_1903015_S-662666.pdf,,,,,,,,,,0.439€,0.364$,10029449-111RLF,,,,,,,,,,,,,,,,,,,,,,,,,,
21,Inductor,L,L1 L2 L3,2.2uH,L_1008_1210,3,http://psearch.en.murata.com/inductor/product/DFE252012PD-2R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,FL001,DFE322512F-2R2M=P2,www.murata.com,DFE322512F-2R2M=P2,Murata,490-10649-1-ND,,,81-DFE322512F-2R2MP2,,C285914,,,,,www.bourns.com,,,Murata,Bourns,,www.murata.com,,,,,,,,,SRP2512A-2R2M,DFE252012P-2R2M=P2,,81-DFE252012P-2R2MP2,0.1082$,,,,,,,,,,,0.48360$,https://datasheet.octopart.com/LQH32PB2R2NN0L-Murata-datashe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,HEI322512A-2R2M-Q8,Chilisin Elec,81-LQH32PB2R2NN0L,,,,,,,,,,,,,,,,,,,,,
22,"Inductor, small symbol",L_Small,L4 L5,33uH,L_0805_2012Metric_Pad1.15x1.40mm_HandSolder,2,~,FL002,,www.bourns.com,CV201210-330K,,CV201210-330KCT-ND,,,652-CV201210-330K,,,,,,,,,,,,,,,,,,,,,,,,,,,,,,,,,,,,,,,,,,,,,,,,,,,,,,,,,,,,,,
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
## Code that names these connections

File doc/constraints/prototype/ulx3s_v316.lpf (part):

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LOCATE COMP "ftdi_ndtr" SITE "N1"; # FPGA receives
LOCATE COMP "ftdi_txden" SITE "L3"; # FPGA receives
LOCATE COMP "ftdi_nrxled" SITE "L5"; # FPGA receives
IOBUF  PORT "ftdi_rxd" PULLMODE=UP IO_TYPE=LVCMOS33 DRIVE=4;
IOBUF  PORT "ftdi_txd" PULLMODE=UP IO_TYPE=LVCMOS33;
IOBUF  PORT "ftdi_nrts" PULLMODE=UP IO_TYPE=LVCMOS33;
IOBUF  PORT "ftdi_ndtr" PULLMODE=UP IO_TYPE=LVCMOS33;
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LOCATE COMP "oled_dc" SITE "P1";   # serdes hdrxp0_d0ch1
LOCATE COMP "oled_csn" SITE "N2";  # serdes hdrxn0_d0ch0
LOCATE COMP "oled_bl" SITE "J4";   # serdes hdrxp0_d0ch0
IOBUF  PORT "oled_clk" PULLMODE=UP IO_TYPE=LVCMOS33 DRIVE=4;
IOBUF  PORT "oled_mosi" PULLMODE=UP IO_TYPE=LVCMOS33 DRIVE=4;
IOBUF  PORT "oled_resn" PULLMODE=UP IO_TYPE=LVCMOS33 DRIVE=4;
IOBUF  PORT "oled_dc" PULLMODE=UP IO_TYPE=LVCMOS33 DRIVE=4;
IOBUF  PORT "oled_csn" PULLMODE=UP IO_TYPE=LVCMOS33 DRIVE=4;
IOBUF  PORT "oled_bl" PULLMODE=UP IO_TYPE=LVCMOS33 DRIVE=4;

## SPI Flash chip "flash" sheet
LOCATE COMP "flash_csn" SITE "R2";
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#LOCATE COMP "flash_cfg_select[2]" SITE "AK4";
IOBUF  PORT "flash_csn" PULLMODE=UP IO_TYPE=LVCMOS33 DRIVE=4;
IOBUF  PORT "flash_clk" PULLMODE=DOWN IO_TYPE=LVCMOS33 DRIVE=4;
IOBUF  PORT "flash_mosi" PULLMODE=UP IO_TYPE=LVCMOS33 DRIVE=4;
IOBUF  PORT "flash_miso" PULLMODE=UP IO_TYPE=LVCMOS33 DRIVE=4;
IOBUF  PORT "flash_holdn" PULLMODE=UP IO_TYPE=LVCMOS33 DRIVE=4;
IOBUF  PORT "flash_wpn" PULLMODE=UP IO_TYPE=LVCMOS33 DRIVE=4;
#IOBUF  PORT "flash_csspin" PULLMODE=UP IO_TYPE=LVCMOS33 DRIVE=4;
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# wifi_gpio2,4,12,13,14,15 are shared with SD card.
# If any of wifi_gpio2,4,12,13 is used in toplevel, don't use sd_d[].
# If SD is used in 1-bit SPI mode, wifi_gpio4,12 = sd_d[1,2] are free,
LOCATE COMP "sd_clk" SITE "H2"; # sd_clk WiFi_GPIO14
LOCATE COMP "sd_cmd" SITE "J1"; # sd_cmd_di (MOSI) WiFi GPIO15
LOCATE COMP "sd_d[0]" SITE "J3"; # sd_d0_do (MISO) WiFi GPIO2
LOCATE COMP "sd_d[1]" SITE "H1"; # sd_d1_irq WiFi GPIO4
LOCATE COMP "sd_d[2]" SITE "K1"; # sd_d2 WiFi_GPIO12
LOCATE COMP "sd_d[3]" SITE "K2"; # sd_d3_csn WiFi_GPIO13
LOCATE COMP "sd_wp" SITE "P5"; # not connected
LOCATE COMP "sd_cdn" SITE "N5"; # not connected
IOBUF  PORT "sd_clk" PULLMODE=UP IO_TYPE=LVCMOS33 DRIVE=4;
IOBUF  PORT "sd_cmd" PULLMODE=UP IO_TYPE=LVCMOS33 DRIVE=4;
IOBUF  PORT "sd_d[0]" PULLMODE=UP IO_TYPE=LVCMOS33 DRIVE=4;
IOBUF  PORT "sd_d[1]" PULLMODE=UP IO_TYPE=LVCMOS33 DRIVE=4;
IOBUF  PORT "sd_d[2]" PULLMODE=NONE IO_TYPE=LVCMOS33 DRIVE=4; # WiFi GPIO12 pulldown bootstrapping without 3.3V efuse
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LOCATE COMP "adc_mosi" SITE "R16";
LOCATE COMP "adc_miso" SITE "U16";
LOCATE COMP "adc_sclk" SITE "P17";
IOBUF  PORT "adc_csn" PULLMODE=UP IO_TYPE=LVCMOS33 DRIVE=4;
IOBUF  PORT "adc_mosi" PULLMODE=UP IO_TYPE=LVCMOS33 DRIVE=4;
IOBUF  PORT "adc_miso" PULLMODE=UP IO_TYPE=LVCMOS33 DRIVE=4;
IOBUF  PORT "adc_sclk" PULLMODE=UP IO_TYPE=LVCMOS33 DRIVE=4;

## Audio 4-bit DAC "analog", "gpio" sheet
# output impedance: 75 ohm
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LOCATE COMP "audio_v[2]" SITE "F5";
LOCATE COMP "audio_v[1]" SITE "F2";
LOCATE COMP "audio_v[0]" SITE "H5";
IOBUF  PORT "audio_l[3]" PULLMODE=NONE IO_TYPE=LVCMOS33 DRIVE=16;
IOBUF  PORT "audio_l[2]" PULLMODE=NONE IO_TYPE=LVCMOS33 DRIVE=16;
IOBUF  PORT "audio_l[1]" PULLMODE=NONE IO_TYPE=LVCMOS33 DRIVE=16;
IOBUF  PORT "audio_l[0]" PULLMODE=NONE IO_TYPE=LVCMOS33 DRIVE=16;
IOBUF  PORT "audio_r[3]" PULLMODE=NONE IO_TYPE=LVCMOS33 DRIVE=16;
IOBUF  PORT "audio_r[2]" PULLMODE=NONE IO_TYPE=LVCMOS33 DRIVE=16;
IOBUF  PORT "audio_r[1]" PULLMODE=NONE IO_TYPE=LVCMOS33 DRIVE=16;
IOBUF  PORT "audio_r[0]" PULLMODE=NONE IO_TYPE=LVCMOS33 DRIVE=16;
IOBUF  PORT "audio_v[3]" PULLMODE=NONE IO_TYPE=LVCMOS33 DRIVE=16;
IOBUF  PORT "audio_v[2]" PULLMODE=NONE IO_TYPE=LVCMOS33 DRIVE=16;
IOBUF  PORT "audio_v[1]" PULLMODE=NONE IO_TYPE=LVCMOS33 DRIVE=16;
IOBUF  PORT "audio_v[0]" PULLMODE=NONE IO_TYPE=LVCMOS33 DRIVE=16;

## WiFi ESP-32 "wifi", "usb", "flash" sheet
# wifi_gpio2,4,12,13,14,15 are shared with SD card.
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LOCATE COMP "wifi_en" SITE "J5"; # enable/reset WiFi
LOCATE COMP "wifi_rxd" SITE "K3"; # FPGA transmits to WiFi
LOCATE COMP "wifi_txd" SITE "K4"; # FPGA receives from WiFi
LOCATE COMP "wifi_gpio0" SITE "F1"; # wifi_en on v3.0.x
LOCATE COMP "wifi_gpio19" SITE "N4"; # wifi_gpio5 on v3.0.x
LOCATE COMP "wifi_gpio21" SITE "K5";
LOCATE COMP "wifi_gpio22" SITE "L2"; # wifi_gpio0 on v3.0.x
LOCATE COMP "wifi_gpio25" SITE "E9";
LOCATE COMP "wifi_gpio26" SITE "L1"; # wifi_gpio16 on v3.0.x
LOCATE COMP "wifi_gpio27" SITE "N3"; # wifi_gpio17 on v3.0.x
LOCATE COMP "wifi_gpio35" SITE "E6"; # FPGA transmits to WiFi
# wifi lines shared with SD card
LOCATE COMP "wifi_gpio2" SITE "J3"; # sd_d0_do (MISO) WiFi GPIO2
LOCATE COMP "wifi_gpio4" SITE "H1"; # sd_d1_irq WiFi GPIO4
LOCATE COMP "wifi_gpio12" SITE "K1"; # sd_d2 WiFi_GPIO12
LOCATE COMP "wifi_gpio13" SITE "K2"; # sd_d3_csn WiFi_GPIO13
LOCATE COMP "wifi_gpio14" SITE "H2"; # sd_clk WiFi_GPIO14
LOCATE COMP "wifi_gpio15" SITE "J1"; # sd_cmd_di (MOSI) WiFi GPIO15
# wifi lines shared with JTAG
# LOCATE COMP "wifi_gpio5" SITE "U5"; # JTAG TMS, blue LED inverted logic
# LOCATE COMP "wifi_gpio18" SITE "T5"; # JTAG TCK
# LOCATE COMP "wifi_gpio23" SITE "R5"; # JTAG TDI
# LOCATE COMP "wifi_gpio34" SITE "V4"; # JTAG TDO
IOBUF  PORT "wifi_en" PULLMODE=UP IO_TYPE=LVCMOS33 DRIVE=4;
IOBUF  PORT "wifi_rxd" PULLMODE=UP IO_TYPE=LVCMOS33 DRIVE=4;
IOBUF  PORT "wifi_txd" PULLMODE=UP IO_TYPE=LVCMOS33 DRIVE=4;
IOBUF  PORT "wifi_gpio0" PULLMODE=UP IO_TYPE=LVCMOS33 DRIVE=4;
IOBUF  PORT "wifi_gpio19" PULLMODE=UP IO_TYPE=LVCMOS33 DRIVE=4;
IOBUF  PORT "wifi_gpio21" PULLMODE=UP IO_TYPE=LVCMOS33 DRIVE=4;
IOBUF  PORT "wifi_gpio22" PULLMODE=UP IO_TYPE=LVCMOS33 DRIVE=4;
IOBUF  PORT "wifi_gpio25" PULLMODE=UP IO_TYPE=LVCMOS33 DRIVE=4;
IOBUF  PORT "wifi_gpio26" PULLMODE=UP IO_TYPE=LVCMOS33 DRIVE=4;
IOBUF  PORT "wifi_gpio27" PULLMODE=UP IO_TYPE=LVCMOS33 DRIVE=4;
IOBUF  PORT "wifi_gpio35" PULLMODE=UP IO_TYPE=LVCMOS33 DRIVE=4;
# wifi lines shared with SD card
IOBUF  PORT "wifi_gpio2" PULLMODE=UP IO_TYPE=LVCMOS33 DRIVE=4;
IOBUF  PORT "wifi_gpio4" PULLMODE=UP IO_TYPE=LVCMOS33 DRIVE=4;
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
## PCB antenna 433 MHz (may be also used for FM) "usb" sheet
LOCATE COMP "ant_433mhz" SITE "G1";
IOBUF  PORT "ant_433mhz" PULLMODE=NONE IO_TYPE=LVCMOS33 DRIVE=4;

## Second USB port "US2" going directly into FPGA "usb", "ram" sheet
LOCATE COMP "usb_fpga_dp" SITE "E16"; # single ended or differential input only
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#LOCATE COMP "jtag_tdo" SITE "V4"; # FTDI_nCTS  FPGA transmits
#LOCATE COMP "jtag_tck" SITE "T5"; # FTDI_nDSR  FPGA receives
#LOCATE COMP "jtag_tms" SITE "U5"; # FTDI_nDCD  FPGA receives
#IOBUF  PORT "jtag_tdi" PULLMODE=UP IO_TYPE=LVCMOS33 DRIVE=4;
#IOBUF  PORT "jtag_tdo" PULLMODE=UP IO_TYPE=LVCMOS33 DRIVE=4;
#IOBUF  PORT "jtag_tck" PULLMODE=UP IO_TYPE=LVCMOS33 DRIVE=4;
#IOBUF  PORT "jtag_tms" PULLMODE=UP IO_TYPE=LVCMOS33 DRIVE=4;

## SDRAM "ram" sheet
LOCATE COMP "sdram_clk" SITE "F19";
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LOCATE COMP "sdram_d[13]" SITE "F18";
LOCATE COMP "sdram_d[14]" SITE "J18";
LOCATE COMP "sdram_d[15]" SITE "J17";
IOBUF PORT "sdram_clk" PULLMODE=NONE IO_TYPE=LVCMOS33 DRIVE=4;
IOBUF PORT "sdram_cke" PULLMODE=NONE IO_TYPE=LVCMOS33 DRIVE=4;
IOBUF PORT "sdram_csn" PULLMODE=NONE IO_TYPE=LVCMOS33 DRIVE=4;
IOBUF PORT "sdram_wen" PULLMODE=NONE IO_TYPE=LVCMOS33 DRIVE=4;
IOBUF PORT "sdram_rasn" PULLMODE=NONE IO_TYPE=LVCMOS33 DRIVE=4;
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IOBUF PORT "gpdi_dn[2]" IO_TYPE=LVCMOS33D DRIVE=4;
IOBUF PORT "gpdi_dp[3]" IO_TYPE=LVCMOS33D DRIVE=4;
IOBUF PORT "gpdi_dn[3]" IO_TYPE=LVCMOS33D DRIVE=4;
IOBUF PORT "gpdi_util" IO_TYPE=LVCMOS33 DRIVE=4;
IOBUF PORT "gpdi_hpd" IO_TYPE=LVCMOS33 DRIVE=4;
IOBUF PORT "gpdi_cec" PULLMODE=UP IO_TYPE=LVCMOS33 DRIVE=4;
IOBUF PORT "gpdi_sda" PULLMODE=UP IO_TYPE=LVCMOS33 DRIVE=4;
IOBUF PORT "gpdi_scl" PULLMODE=UP IO_TYPE=LVCMOS33 DRIVE=4;

# GPIO (default single-ended) "gpio", "ram", "gpdi" sheet
# Pins enumerated gp[0-27], gn[0-27].
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
## PROGRAMN (reload bitstream from FLASH, exit from bootloader)
LOCATE COMP "user_programn" SITE "M4";
IOBUF  PORT "user_programn" PULLMODE=UP IO_TYPE=LVCMOS33 DRIVE=4;

## SHUTDOWN "power", "ram" sheet
LOCATE COMP "shutdown" SITE "G16"; # FPGA receives
IOBUF  PORT "shutdown" PULLMODE=DOWN IO_TYPE=LVCMOS33 DRIVE=4;

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
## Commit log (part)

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2020-10-01 PCB: thicker GND
2020-10-01 PCB: thicken 3.3V bridge
2020-10-01 todo update
2020-10-01 schematics: switch to serdes symbol
2020-10-01 PCB: re-run DRC for switched serdes symbol
2020-10-02 schematics: serdes power
2020-10-02 PCB: serdes power
2020-10-02 PCB: serdes RX disconnected from GND
2020-10-02 footprints: global for R and C
2020-10-02 PCB: serdes trac cosmetix
2020-10-02 schematics: rename sdcard->serdes sheet
2020-10-02 footprints: BGA 4th aligment cross, now aligment in all 4 corners
2020-10-02 PCB: BGA alignment crosses in all 4 corners
2020-10-02 gerbers: PCB v3.1.3? (preliminary)
2020-10-03 todo: FT231 too close to LCD holes
2020-10-04 manual update
2020-10-04 manual
2020-10-05 footprints: SDRAM silkscreen center
2020-10-05 PCB: use new footprints for FPGA and SDRAM with centers
2020-10-13 micro-sd molex 104031-0811 push-pull new footprint
2020-10-13 PCB: new SD footprint
2020-10-13 footprints: thicker SD1
2020-10-14 footprints: table updated
2020-10-14 PCB: network around D28 moved away from LCD connector, logotypes returned
2020-10-14 README friendly->compatible
2020-10-14 1-click bom updated
2020-10-14 1-click bom
2020-10-16 footprints: combo old and new SD footprint
2020-10-16 ulx3s-cache.lib
2020-10-16 schematics: SD card for new footprint
2020-10-16 PCB: move MOSI resistor near FLASH
2020-10-16 schematics: footprint SD
2020-10-16 PCB: trac cosmetix
2020-10-18 AN108 adapter link
2020-10-18 schematics: SD card no pin 9
2020-10-18 schematics: serdes capacitors
2020-10-18 schematics: label for v3.1.3 as preparation (still some things todo)
2020-10-18 PCB: serdes capactiros routed
2020-10-18 schematics: serdes clock only on 0, it can be shared internally
2020-10-18 PCB: update
2020-10-18 todo
2020-10-18 schematics: sort GPDI capacitors
2020-10-18 PCB: return of logos and silkscreen cosmetix
2020-10-18 schematics: C for serdes TX
2020-10-19 schematics: 10k HPD resistor
2020-10-19 schematics: ulx3s.pro updated v3.1.3
2020-10-19 PCB: v3.1.3 preliminary
2020-10-19 gerbv.gvp project update to see holes
2020-10-19 footprints: GPDI THT paste openings
2020-10-19 gerbers: Paste layer update
2020-10-19 schematics: D30 zener 3.6V for HPD protection and 549 ohm resistor
2020-10-19 PCB: D30 protection zener 3.6V for GPDI HPD
2020-10-19 gerbers: update
2020-10-19 schematics: fix wrong placed zener D30 at gpdi
2020-10-19 PCB, gerbers: route new zener D30
2020-10-31 PCB: move C18, R24 more inside, away from the edge
2020-10-31 PCB: v3.1.4 preliminary, with FT231XQ QFN-20
2020-10-31 schematics: FT231XQ PNs
2020-11-01 footprints: FT231XQ with 2x2mm pad
2020-11-01 schematics: use FT231XQ footprint with 2x2mm pad
2020-11-01 pdf schematics: v3.1.4
2020-11-01 floorplan: assembly bottom U6 FT231XQ
2020-11-01 gerbers: v3.1.4
2020-11-01 PCB: batter polarity signs and bold "RS232", "WROOM", "WROVER"
2020-11-01 PCB: battery signs (+) (-) moving
2020-11-01 gerbers: battery signs (+),(-) silkscreen
2020-11-02 PCB: use footprint with battery polarity
2020-11-02 gerbers: silkscreen update battery polarity
2020-11-02 1-click-bom.tsv: 220nF->22nF GPDI
2020-11-02 PCB: 220nF->22nF GPDI
2020-11-02 PCB: silkscreen logo footprints made "virtual", avoid placement
2020-11-02 gerbers: avoid placement virtual footprints for logos
2020-11-02 PCB: RV3 mounted
2020-11-02 footprints: FT231XQ pin 1 dot mark
2020-11-02 PCB: FT231XQ pin1 dot mark
2020-11-04 PCB: RV3 visible on 3D view
2020-11-06 footprints: no solder paste for 4 WROOM pins
2020-11-06 gerbers: paste layer update for ESP32 no 4 WROOM pins
2020-11-07 PCB: silkscreen remove description from 3.5mm audio jack
2020-11-12 PCB: trac cosmetix, delete hidden track on the pad of 3.3V C under BGA
2020-11-16 schematics: update mouser PN for available 220nF
2020-11-16 schematics: update mouser and digikey available PN for 2.2uH inductor
2020-11-16 schematics: digikey available PN for 100k resistor
2020-11-16 schematics: untested mouser PN TI switcher 1.5A (not default)
2020-11-16 schematics: 470pF->100pF
2020-11-16 schematics: digikey PN for 85F
2020-11-16 1-click-bom.tsv: digikey PN for 85F
2020-11-16 schematics: SD card slot for LCSC and digikey
2020-11-16 1-click-bom.tsv: SD card slot for digikey and LCSC, non-stocked 45F at LCSC
2020-11-17 schematics: LCSC PN 2.2uH inductor
2020-11-17 pic: update v3.1.4
2020-11-18 schematics: newark PNs for some semiconductors and connectors (not all)
2020-11-18 schematics: Newark PN switches
2020-11-18 1-click-bom.tsv: newark PN switches
2020-11-18 1-click-bom.tsv: newark PN capacitors
2020-11-18 1-click-bom.tsv: temporarily use DIO6015B switcher currently Mouser on-stock
2020-11-19 1-click-bom.tsv: LEN PN Newark
2020-11-19 schematics: PN Newark pushbutton
2020-11-20 schematics: PN newark R, pushbutton
2020-11-20 1-click-bom.tsv: PN newark R, pushbutton
2020-11-20 1-click-bom.tsv: PN newark 100k
2020-11-20 schematics: fix PN newark mistake at BAT1
2020-11-20 schematics: PN newark, lcsc R
2020-11-20 1-click-bom.tsv: PN newark, lcsc R
2020-11-28 1-click BOM update
2020-11-30 manual update, what's different between board versions
2020-11-30 manual SD types
2020-11-30 manual typo
2020-11-30 readme, serdes fix
2020-12-06 serdes: place "x" for unconnected lines
2020-12-06 gerbers: 470pF->100pF
2020-12-24 3D st7789 holder longer pins
2020-12-25 box with small adjustments for v3.1.x boards
2021-01-14 README.md: Fix broken link to FPGA datasheet
    I'm pretty sure it is the right one because they kept the same document identifier, only the base URL changed.
2021-01-25 schematics v3.1.5 note on swapping WIFI_EN - WIFI_GPIO22
2021-02-17 gerbers v3.1.5
2021-02-17 pictures 3D v3.1.5
2021-02-17 symlink to schematics v3.1.5
2021-02-17 PCB: thicken lines near flash chip 0.127->0.19 mm
2021-02-17 gerbers v3.1.5 thicken flash lines, ant 433 straighten, bga flood small update
2021-02-17 PCB thermal management on bottom layer near 2.5V switcher
2021-02-17 symlinks
2021-02-25 schematics: BOM update with currently available mouser PN's
2021-02-26 schematics: PN alternatives for dialight red and orange LEDs
2021-02-27 manual: v3.1.x note how to unbrick ESP32 if it drives PIN 5 (wifi_gpio5, blue LED) immediately after boot.
2021-02-27 schematics: v3.1.6 preliminary, WIFI_GPIO0 and WIFI_GPIO22 swapped
2021-02-27 constraints for v3.1.4 and v3.1.6
2021-02-28 gerbers: v3.1.6
2021-02-28 symlink to schematics v3.1.6
2021-02-28 ulx3s.pro refreshed
2021-03-01 PCB: move AUDIO1 connector down, pad was over the edge
2021-03-01 gerbers: AUDIO1 moved down, pad inside the edge of PCB now
2021-03-01 gerbers: moving AUDIO1 down and updating insertion positions
2021-03-02 PCB: R55 do not install (should not shown on top floorplan)
2021-03-04 ulx3s mention USB-PS/2 keyboard reported working
2021-03-11 correct relative path for micro sd schematics symbol
2021-03-11 1-click bom: currently available mouser PN for L1,2,3 inductors
2021-03-13 schematics: mouser PN SDRAM winbond
2021-03-15 schematics: mouser available PN for 2.2uF
2021-03-15 1-click-bom: mouser available PN for 2.2uF
2021-03-30 PCB: straightening tracks in purple and red layer
2021-04-20 manual 3.5 mm OMTP cable description
2021-05-23 R56 makes ESP32 boot standalone without any help of FPGA bitstream
2021-05-23 schematics USB cleanup from old FT231X R56 note
2021-05-23 gerbers v3.1.7
2021-05-23 PDF schematics v3.1.7
2021-05-23 3D model pic v3.1.7
2021-05-23 schematics: update mouser PN's
2021-05-23 1-click-bom with updated mouser PNs
2021-05-24 1-click-bom SI diode PN
2021-05-24 move gerbers to plot/gerbers directory and symlinks
2021-05-24 point kitspace to plot/gerbers directory
2021-05-24 cleanup remove drill map
2021-05-24 1-click-bom.tsv: micro usb mouser PN
2021-05-24 schematics: few resistors mouser PN update
2021-05-25 manual v3.1.6 to v3.1.7 upgrade
2021-06-05 new boards
2021-06-05 constraints for v2.x.x and v3.0.x update
2021-06-10 experimental panelization makefile
2021-06-11 panel: fix area and tolerace to let all board parts included
2021-06-11 maybe better panelization with tabs
2021-06-11 some tabs improvement, not yet fully
2021-06-12 pictures of v3.1.6 prototypes
2021-06-12 panelizing near what Koncar did, one detail missing, mill cut should be extended few mm left and right
2021-06-12 panelization makefile cleanup
2021-06-13 panelizing comments about trying some options to enlarge mill cuts, but don't make wanted result yet
2021-06-13 panelization workaround radius 0 until better option is found
2021-06-13 PCB: removing Cmt layer drawing from 4 mounting holes 3.2 mm
2021-06-13 footprints: remove Cmt layer lines from micro USB
2021-06-13 PCB: separating D10-D13 D16-D27
2021-06-13 PCB: text for panelization workaround: IGNORE THIS EDGE CUT, USE PANEL MILL
2021-06-13 gerbv project for panel edge cut on top, drill holes gray to become visible
2021-06-14 readme panel update
2021-06-14 readme update
2021-06-14 readme panelization update
2021-06-14 gerbv project update panel colors
2021-06-14 readme panelization, advanced options
2021-06-14 panelization makefile: generate rar file and "make view" to open with pcbnew
2021-06-14 gerbv project, copper color
2021-07-07 typo
2021-07-12 PCB: write note to ignore rectangle cut from paste layer (stencil) until kikit bugs are fixed
2021-07-14 notes for future kikit version
2021-07-14 gerbers: hopfully cleaner notes to manufacturer what areas on PCB panel should remain
2021-08-05 1-click bom mouser PNs update
2021-08-24 manual fujprog replaced with openFPGALoader script
2021-08-24 fujprog->openFPGALoader replacement moved to programming US1 description
2021-08-24 new panelization nearly ok
2021-08-24 almost good, bug cutting stencil
2021-08-24 run panelization twice for stencil bug workaround
2021-08-25 cleanup, stencil, fiducials
2021-08-25 no more stencil bugs (fixed in latest kikit)
2021-08-25 makefile panelization date, cleanup
2021-08-25 panelization source tolerance 20 mm
2021-08-25 PCB: update for new panelization, no more visible comments needed
2021-08-25 makefile comments
2021-08-26 set path in panel rar archive
2021-08-26 new kikit install in plot readme
2021-08-26 pad count with gerbv
2021-08-26 JLCPCB pads charge
2021-08-26 cleanup
2021-08-26 rar file path
2021-08-26 move legacy makefile to old
2021-08-26 schematics: PN for currently availabe switcher IC
2021-08-26 1-click bom switcher IC DIO6012B 6-pin
2021-08-27 panel mill 2mm
2021-08-27 readme panel mill 2 mm
2021-08-27 schematics: Update mouser PNs
2021-08-27 updated mouser PNs
2021-08-27 board size updated
2021-08-28 add 4 tooling holes and simplify makefile for panelization
2021-09-03 schematics: SDRAM Mouser PN
2021-09-03 1-click BOM: SDRAM Mouser PN
2021-09-03 schematics: DIP SW Mouser PN
2021-09-30 box: rear panel with a hole for 40-pin female connector
2021-09-30 box: front panel text cut option
2021-10-01 box rounding 2->3 mm
2021-10-07 new production
2021-10-07 updated produced boards and memory parts
2021-10-07 manual, new DFU bootloader
2021-10-09 footprints: D&M logo
2021-10-09 PCB: more logos
2021-10-09 footprints: D&M logo fix
2021-10-09 PCB: use OSHW logo
2021-10-29 manual, updated links to precompiled tools for all platforms
2021-10-29 last opensource nightly build
2021-10-29 manual, kost tools comments
2021-11-12 makefile panel: fixes error can't V-Cut a curve
2021-11-13 footprints: ABS07 32768Hz crystal
2021-11-13 schematics: footprint for ABS07 crystal
2021-11-13 1-click BOM: ABS07 crystal
2021-11-15 snap box
2021-11-15 button pin
2021-11-15 plastic box manual short info
2021-11-15 small hint in .scad file
2021-11-16 snapbox: updated dim's and printing comments
2021-11-16 footprints workaround symlink
2021-11-17 box expert system: enlarging for 1.54" ST7789
2021-11-17 box more dim's
2021-11-19 box side header support
2021-11-20 separate ulx3s_pcb include, fix for header_type, side and display cut fix
2021-11-28 LAN8720 updated link
2021-11-28 readme typo
2021-12-10 pdf schematics: update with banks marked "not differential"
2021-12-24 manual: openFPGALoader in DFU mode
2022-01-14 manual, produced quantity 8+168
2022-01-14 manual production, remove "-TR" to SDRAM PN
2022-01-14 manual: v3.1.7 will be sold at Mouser ...
2023-01-13 README.md: Fix broken link to SDRAM datasheet
